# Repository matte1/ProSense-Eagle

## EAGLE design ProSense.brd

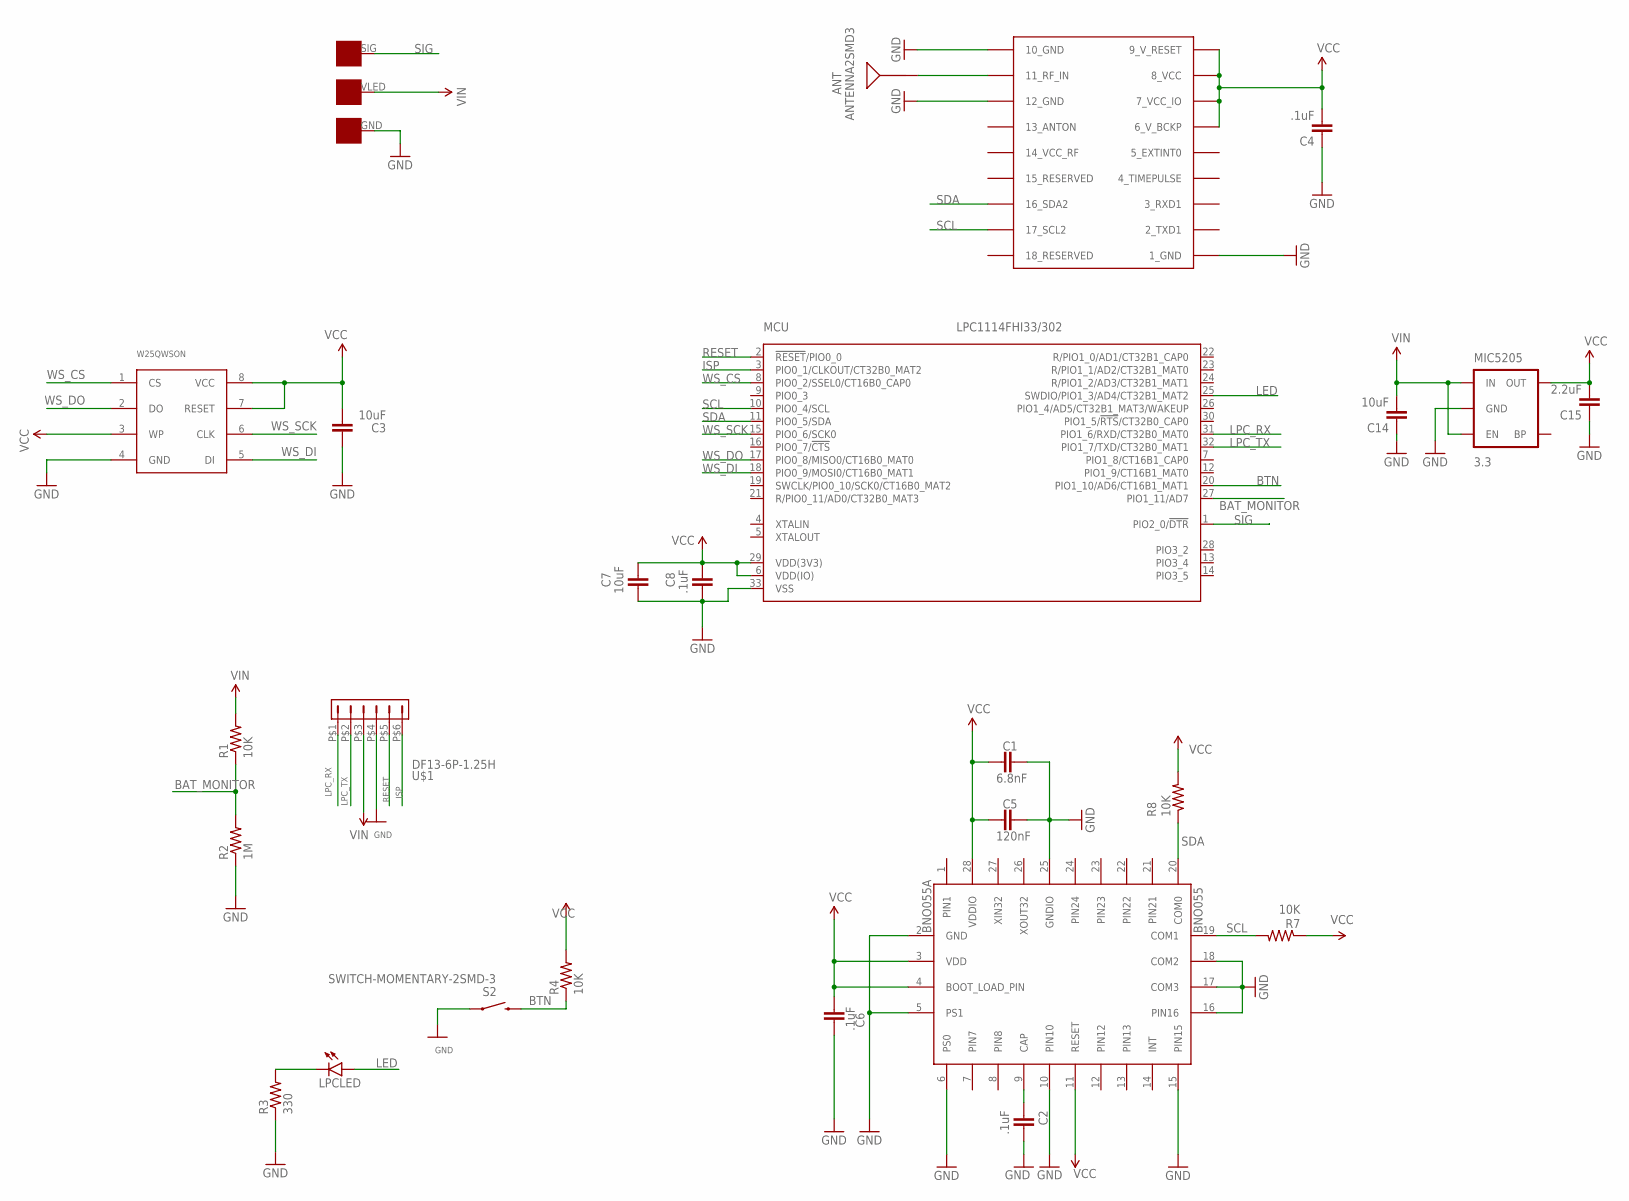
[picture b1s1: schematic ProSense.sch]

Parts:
ANT: ANTENNA2SMD3; ANTENNA-CHIP4
BNO055: BNO055A; BNO055
C1: 6.8nF; 0603-CAP
C2, C4, C6, C8: .1uF; 0603-CAP
C3, C7, C14: 10uF; 0603-CAP
C5: 120nF; 0603-CAP
C15: 2.2uF; 0603-CAP
LPCLED: LED0603; LED-0603
MCU: LPC1114FHI33/302; SOT617-3
MIC5205: 3.3; SOT23-5
R1, R4, R7, R8: 10K; 0603-RES
R2: 1M; 0603-RES
R3: 330; 0603-RES
S2: SWITCH-MOMENTARY-2SMD-3; TACTILE_SWITCH_SMD-3
U$1: DF13-6P-1.25H; DF13A-6P-1.25H
U$2: UBLOX_MAX
U$4: CON; COPPER-PAD
W25QWSON: W25Q128FVWSON; WSON-8-PAD

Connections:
BAT_MONITOR: MCU.27 (PIO1_11/AD7), R1.1, R2.2
BTN: MCU.20 (PIO1_10/AD6/CT16B1_MAT1), R4.1, S2.4 (2)
GND: BNO055.2 (GND), BNO055.5 (PS1), BNO055.6 (PS0), BNO055.10 (PIN10), BNO055.15 (PIN15), BNO055.16 (PIN16), BNO055.17 (COM3), BNO055.18 (COM2), BNO055.25 (GNDIO), C1.1, C2.1, C3.1, C4.1, C5.1, C6.2, C7.2, C8.2, C14.1, C15.1, MCU.33 (VSS), MIC5205.2 (GND), R2.1, R3.1, S2.1, U$1.P$4 (4), U$2.1_GND, U$2.10_GND, U$2.12_GND, U$4.GND, W25QWSON.4 (GND)
ISP: MCU.3 (PIO0_1/CLKOUT/CT32B0_MAT2), U$1.P$6 (6)
LED: LPCLED.A, MCU.25 (SWDIO/PIO1_3/AD4/CT32B1_MAT2)
LPC_RX: MCU.31 (PIO1_6/RXD/CT32B0_MAT0), U$1.P$1 (1)
LPC_TX: MCU.32 (PIO1_7/TXD/CT32B0_MAT1), U$1.P$2 (2)
unnamed: ANT.SIG, U$2.11_RF_IN
unnamed: BNO055.9 (CAP), C2.2
unnamed: LPCLED.C, R3.2
RESET: MCU.2 (!RESET!/PIO0_0), U$1.P$5 (5)
SCL: BNO055.19 (COM1), MCU.10 (PIO0_4/SCL), R7.2, U$2.17_SCL2
SDA: BNO055.20 (COM0), MCU.11 (PIO0_5/SDA), R8.1, U$2.16_SDA2
SIG: MCU.1 (PIO2_0/!DTR!), U$4.SIG
VCC: BNO055.3 (VDD), BNO055.4 (BOOT_LOAD_PIN), BNO055.11 (RESET), BNO055.28 (VDDIO), C1.2, C3.2, C4.2, C5.2, C6.1, C7.1, C8.1, C15.2, MCU.6 (VDD(IO)), MCU.29 (VDD(3V3)), MIC5205.5 (OUT), R4.2, R7.1, R8.2, U$2.6_V_BCKP, U$2.7_VCC_IO, U$2.8_VCC, U$2.9_V_RESET, W25QWSON.3 (WP), W25QWSON.7 (RESET), W25QWSON.8 (VCC)
VIN: C14.2, MIC5205.1 (IN), MIC5205.3 (EN), R1.2, U$1.P$3 (3), U$4.VLED
WS_CS: MCU.8 (PIO0_2/SSEL0/CT16B0_CAP0), W25QWSON.1 (CS)
WS_DI: MCU.18 (PIO0_9/MOSI0/CT16B0_MAT1), W25QWSON.5 (DI)
WS_DO: MCU.17 (PIO0_8/MISO0/CT16B0_MAT0), W25QWSON.2 (DO)
WS_SCK: MCU.15 (PIO0_6/SCK0), W25QWSON.6 (CLK)

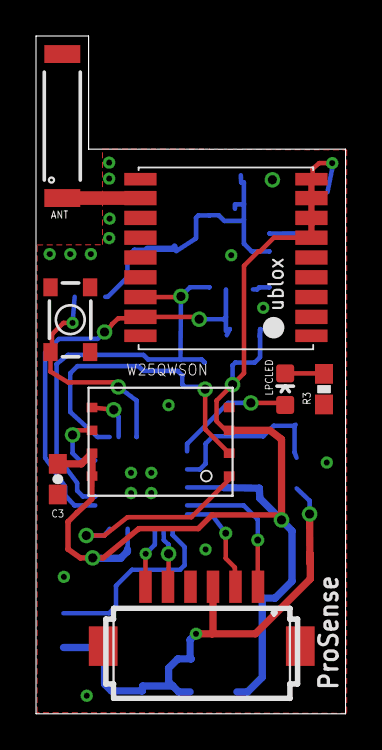
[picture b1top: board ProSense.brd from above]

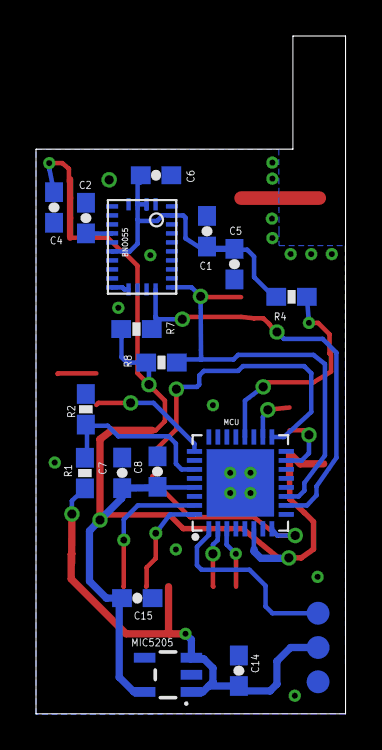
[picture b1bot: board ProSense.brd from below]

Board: 2 copper layers, 17.2 x 37.7 mm, 26 parts (18 on the bottom side), 20 nets.

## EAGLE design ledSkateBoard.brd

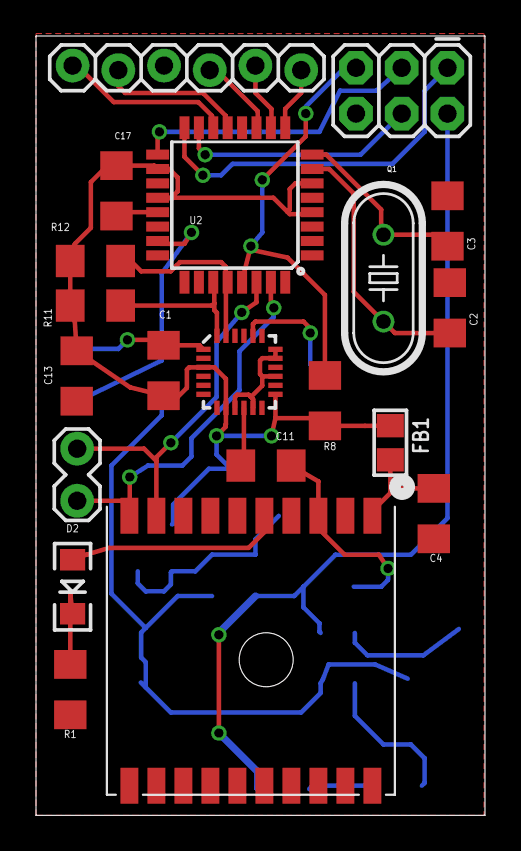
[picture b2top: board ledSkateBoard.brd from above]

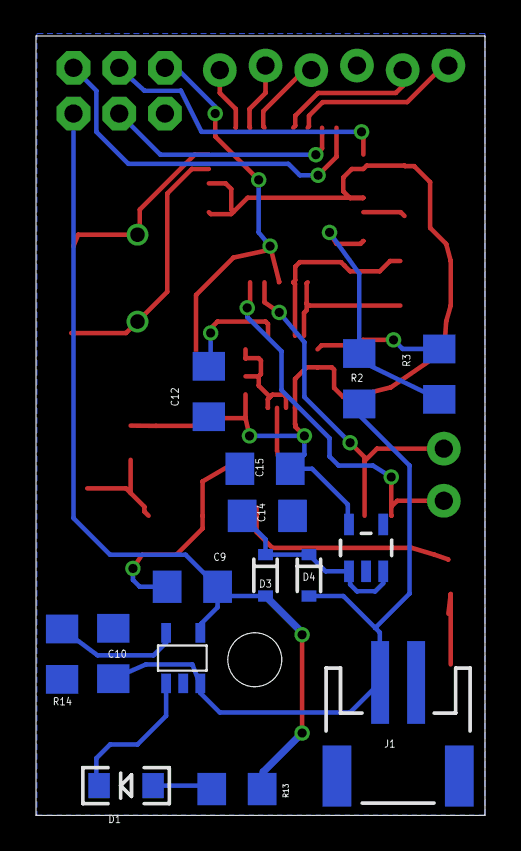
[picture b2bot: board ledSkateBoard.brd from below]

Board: 2 copper layers, 24.9 x 43.3 mm, 35 parts (15 on the bottom side), 29 nets.

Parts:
C1: 10nF; 1206
C2, C3: 22pF; 1206
C4, C14, C15, C17: 10uF; 1206
C9, C10: 4.7uF; 1206
C11, C13: .1uF; 1206
C12: 2.2nF 50V; 1206
D1: RED; LED-1206
D2: GREEN; LED-1206
D3, D4: PMEG4005EJ; SOD-323
FB1: 0805
J1: JST; JST-2-SMD
JP1: AVR_SPI_PRG_6PTH; 2X3
JP2: 1X06_LOCK
JP3: M02LOCK; 1X02_LOCK
Q1: 16Mhz; HC49/S
R1, R13: 330; 1206
R2: 37K; 1206
R3: 430K; 1206
R8: 1K; 1206
R11, R12: 4.7K; 1206
R14: 2K; 1206
U1: MPU-9150; QFN-24-NP
U2: ATMEGA328P_TQFP; TQFP32-08
U3: FGPMMOPA6H
U4: MIC2505 3.3; SOT23-5
U$1: MCP73831; SOT23-5

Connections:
5V: C9.1, D3.A, JP1.2, R13.2, U$1.4
AN0: JP2.2, U2.10
AN1: JP2.3, U2.11
GND: C1.1, C2.2, C3.2, C4.2, C9.2, C10.2, C11.2, C12.2, C13.1, C14.1, C15.1, C17.1, J1.1, JP1.6, R1.2, R3.1, R14.1, U1.1, U1.9, U1.11, U1.15, U1.17, U1.18, U2.3, U2.5, U2.21, U3.P$3, U3.P$8, U3.P$19, U4.2, U$1.2
GPS_RX: JP3.2, U2.31, U3.P$10
GPS_TX: JP3.1, U2.30, U3.P$9
MISO: JP1.1, U2.16
MOSI: JP1.4, U2.15
unnamed: C11.1, U1.10
unnamed: C12.1, U1.20
unnamed: C2.1, Q1.2, U2.7
unnamed: C4.1, FB1.1, U3.P$1
unnamed: C3.1, Q1.1, U2.8
unnamed: D2.A, U3.P$5
unnamed: D1.A, R13.1
unnamed: D1.C, U$1.1
unnamed: D2.C, R1.1
unnamed: C14.2, D3.C, D4.C, U4.1, U4.3
unnamed: R14.2, U$1.5
PB1: JP2.5, U2.13
PB2: JP2.6, U2.14
PD5: JP2.1, U2.9
PWR_MNTR: R2.1, R3.2, U2.23
RESET: JP1.5, R8.1, U2.29
SCK: JP1.3, U2.17
SCL: R12.1, U1.23, U2.28
SDA: R11.1, U1.24, U2.27
VCC: C1.2, C13.2, C15.2, C17.2, FB1.2, R8.2, R11.2, R12.2, U1.3, U1.8, U1.13, U2.4, U2.6, U2.18, U2.20, U4.5
V_BATT: C10.1, D4.A, J1.2, R2.2, U$1.3

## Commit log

2015-02-19 Initial commit w/ schematic
2015-02-19 Added PDF
2015-02-23 Initial route of board
    Still need to add test pads for debugging.
2015-02-26 Final version before ordering.
2015-03-13 Updated PDF and added BOM
2015-03-13 Learned how to use Smash tool. Redid silkscreen
2015-04-02 Final on revA
2015-04-25 Final
2015-05-12 Changed to lpc1114 and BNO055
2015-05-12 Added pdfs
2015-05-16 faileld attempt
2015-05-17 semi final version pending review
2015-05-19 squelch
2015-05-19 Initial design
2015-05-22 Closer..
2015-05-23 squash
2015-06-18 v1.1
2015-07-02 fixup
2015-07-25 Finished rev 1.2.1
2015-07-26 Initial commit for QFN Package
2015-11-04 Initial Revision for QFN packages
2015-11-13 Fixed up a few things. Need to fix ground pads and holes for qfn
2015-11-14 Added Measurements
2015-12-23 improved wiring
2015-12-24 MTK3339 readded
2016-04-21 Added pdfs of schematic and board

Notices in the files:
parts and their libraries:
SparkFun-Passives: Licensing: Creative Commons ShareAlike 4.0 International - https://creativecommons.org/licenses/by-sa/4.0
NXP_60_26022015: This library may be distributed and adapted freely for any purpose, as long as NXP is credited and any new creation is licensed under the same terms.
